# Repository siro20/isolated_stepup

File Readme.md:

# Isolated 12VDC to 300VDC SMPS

This project is about finding a power supply to drive regular 240VAC/120VAC
LED bulbs from a 12V power supply or 12V battery.

This is the first prototype build using the [LTC3723](https://www.analog.com/media/en/technical-documentation/data-sheets/372312f.pdf).

It features:
- Up to 32 Watts
- LC input filter
- Soft-start
- 3 Amps input current limit
- Galvanic isolation
- Adjustable output voltage (for development only)

## Analysis

Measured results of version `0.2`.
- [soft-start](doc/softstart.md)

## Schematics

## Safety advice

    Design, installation and inspection of machinery and devices carrying high voltage
    require accordingly trained and qualified personnel.
    Appropriate safety rules and directives must be complied with.
    Improper handling of high voltage can mean severe injuries or death and may cause
    serious collateral damage! 

## Disclaimer

    THE OPEN SOURCE SOFTWARE/HARDWARE IN THIS PROJECT IS DISTRIBUTED
    IN THE HOPE THAT IT WILL BE USEFUL, BUT WITHOUT ANY WARRANTY, WITHOUT
    EVEN THE IMPLIED WARRANTY OF MERCHANTABILITY OR FITNESS FOR A
    PARTICULAR PURPOSE.

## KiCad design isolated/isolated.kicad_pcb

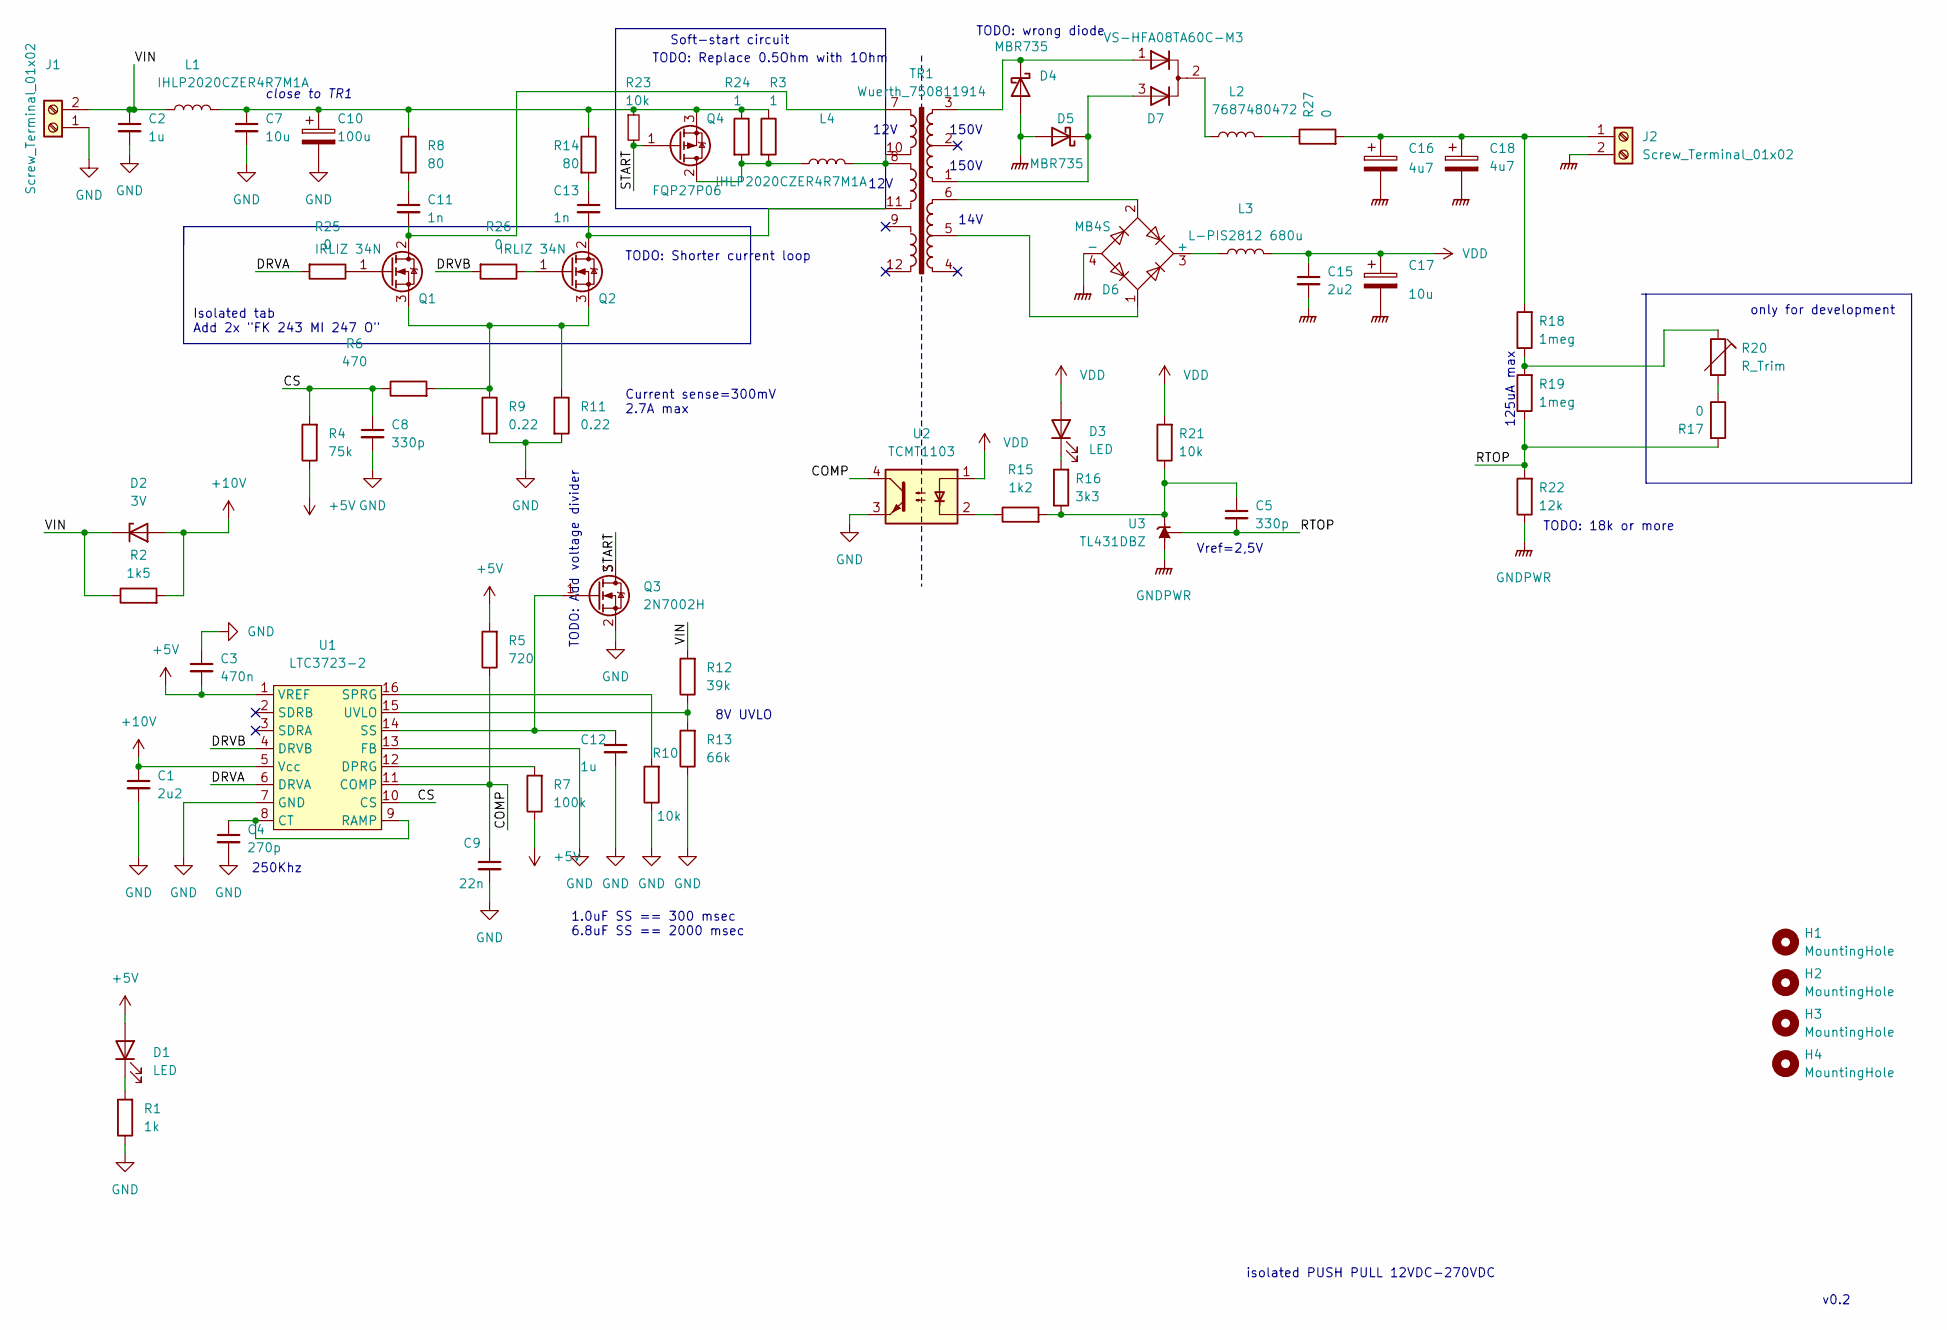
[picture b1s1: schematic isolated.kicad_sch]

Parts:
C1, C15: 2u2; C_1210_3225Metric_Pad1.33x2.70mm_HandSolder
C2, C12: 1u; C_1210_3225Metric_Pad1.33x2.70mm_HandSolder
C3: 470n; C_0805_2012Metric_Pad1.18x1.45mm_HandSolder
C4: 270p; C_0603_1608Metric_Pad1.08x0.95mm_HandSolder
C5, C8: 330p; C_0603_1608Metric_Pad1.08x0.95mm_HandSolder
C7: 10u; C_1210_3225Metric_Pad1.33x2.70mm_HandSolder
C9: 22n; C_0603_1608Metric_Pad1.08x0.95mm_HandSolder
C10: 100u; C_Radial_D10.0mm_H12.5mm_P5.00mm
C11, C13: 1n; C_0805_2012Metric_Pad1.18x1.45mm_HandSolder
C16, C18: 4u7; C_Radial_D12.5mm_H20.0mm_P5.00mm
C17: 10u; C_Radial_D8.0mm_H11.5mm_P3.50mm
D1, D3: LED; LED_D3.0mm_Clear
D2: 3V; D_DO-34_SOD68_P2.54mm_Vertical_KathodeUp
D4, D5: MBR735; TO-220-2_Vertical
D6: MB4S; TO-269AA
D7: VS-HFA08TA60C-M3; TO-220-3_Vertical
H1, H2, H3, H4: MountingHole; MountingHole_2.7mm_M2.5_DIN965_Pad
J1, J2: Screw_Terminal_01x02; PhoenixContact_MCV_1,5_2-G-5.08_1x02_P5.08mm_Vertical
L1, L4: IHLP2020CZER4R7M1A; L_Sunlord_MWSA05xxS
L2: 7687480472; L_Radial_D12.0mm_P5.00mm_Neosid_SD12_style2
L3: L-PIS2812 680u; L_Vishay_IHLP-2020
Q1, Q2: IRLIZ 34N; TO-220-3_Vertical
Q3: 2N7002H; SOT-23
Q4: FQP27P06; TO-220-3_Vertical
R1: 1k; R_0805_2012Metric_Pad1.20x1.40mm_HandSolder
R2: 1k5; R_0805_2012Metric_Pad1.20x1.40mm_HandSolder
R3, R24: 1; R_1206_3216Metric_Pad1.30x1.75mm_HandSolder
R4: 75k; R_0805_2012Metric_Pad1.20x1.40mm_HandSolder
R5: 720; R_0805_2012Metric_Pad1.20x1.40mm_HandSolder
R6: 470; R_0805_2012Metric_Pad1.20x1.40mm_HandSolder
R7: 100k; R_0805_2012Metric_Pad1.20x1.40mm_HandSolder
R8, R14: 80; R_1206_3216Metric_Pad1.30x1.75mm_HandSolder
R9, R11: 0.22; R_2512_6332Metric_Pad1.40x3.35mm_HandSolder
R10, R21, R23: 10k; R_0805_2012Metric_Pad1.20x1.40mm_HandSolder
R12: 39k; R_0805_2012Metric_Pad1.20x1.40mm_HandSolder
R13: 66k; R_0805_2012Metric_Pad1.20x1.40mm_HandSolder
R15: 1k2; R_0805_2012Metric_Pad1.20x1.40mm_HandSolder
R16: 3k3; R_0805_2012Metric_Pad1.20x1.40mm_HandSolder
R17: 0; R_0805_2012Metric
R18: 1meg; R_Axial_DIN0309_L9.0mm_D3.2mm_P5.08mm_Vertical
R19: 1meg; R_Axial_DIN0207_L6.3mm_D2.5mm_P5.08mm_Vertical
R20: R_Trim; Potentiometer_Bourns_3386C_Horizontal
R22: 12k; R_0805_2012Metric_Pad1.20x1.40mm_HandSolder
R25, R26: 0; R_0805_2012Metric_Pad1.20x1.40mm_HandSolder
R27: 0; R_1206_3216Metric_Pad1.30x1.75mm_HandSolder
TR1: Wuerth_750811914; 750811914
U1: LTC3723-2; SSOP-16_3.9x4.9mm_P0.635mm
U2: TCMT1103; SOP-4_4.4x2.6mm_P1.27mm
U3: TL431DBZ; SOT-23

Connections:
+5V: C3.2, D1.2 (A), R4.1, R5.2, R7.1, U1.1 (VREF)
+10V: C1.1, D2.2 (A), R2.2, U1.5 (Vcc)
/COMP: C9.1, R5.1, U1.11 (COMP), U2.4
/CS: C8.1, R4.2, R6.1, U1.10 (CS)
/DRVA: R25.2, U1.6 (DRVA)
/DRVB: R26.2, U1.4 (DRVB)
/RTOP: C5.2, R17.2, R19.1, R22.2, U3.2 (REF)
/START: Q3.3 (D), Q4.1 (G), R23.2
/VIN: C2.1, D2.1 (K), J1.2, L1.1, R2.1, R12.2
GND: C1.2, C2.2, C3.1, C4.2, C7.2, C8.2, C9.2, C10.2, C12.2, J1.1, Q3.2 (S), R1.1, R9.2, R10.1, R11.2, R13.1, U1.7 (GND), U1.13 (FB), U2.3
GNDPWR: C15.2, C16.2, C17.2, C18.2, D4.2 (A), D5.2 (A), D6.4 (-), J2.2, R22.1, U3.3 (A)
unnamed: C4.1, U1.8 (CT), U1.9 (RAMP)
unnamed: C5.1, R15.2, R16.1, R21.1, U3.1 (K)
unnamed: C11.1, R8.2
unnamed: C11.2, Q1.2 (D), TR1.7
unnamed: C12.1, Q3.1 (G), U1.14 (SS)
unnamed: C13.1, R14.2
unnamed: C13.2, Q2.2 (D), TR1.11
unnamed: C16.1, C18.1, J2.1, R18.2, R27.2
unnamed: D1.1 (K), R1.2
unnamed: D3.1 (K), R16.2
unnamed: D4.1 (K), D7.1 (K), TR1.3
unnamed: D5.1 (K), D7.3 (K), TR1.1
unnamed: D7.2 (A), L2.1
unnamed: L2.2, R27.1
unnamed: D6.3 (+), L3.1
unnamed: L4.1, Q4.2 (D), R3.2, R24.2
unnamed: L4.2, TR1.8, TR1.10
unnamed: Q1.1 (G), R25.1
unnamed: Q2.1 (G), R26.1
unnamed: Q1.3 (S), Q2.3 (S), R6.2, R9.1, R11.1
unnamed: C7.1, C10.1, L1.2, Q4.3 (S), R3.1, R8.1, R14.1, R23.1, R24.1
unnamed: R7.2, U1.12 (DPRG)
unnamed: R10.2, U1.16 (SPRG)
unnamed: R12.1, R13.2, U1.15 (UVLO)
unnamed: R15.1, U2.2
unnamed: R17.1, R20.2
unnamed: R18.1, R19.2, R20.1
unnamed: D6.1, TR1.5
unnamed: D6.2, TR1.6
VDD: C15.1, C17.1, D3.2 (A), L3.2, R21.2, U2.1

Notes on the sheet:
12V
TODO: 18k or more
Isolated tab Add 2x "FK 243 MI 247 O"
TODO: Add voltage divider
150V
only for development
250Khz
TODO: Shorter current loop
1.0uF SS == 300 msec 6.8uF SS == 2000 msec
Soft-start circuit
Vref=2,5V
8V UVLO
close to TR1
TODO: Replace 0.5Ohm with 1Ohm
v0.2
125uA max
TODO: wrong diode
Current sense=300mV 2.7A max
isolated PUSH PULL 12VDC-270VDC
14V

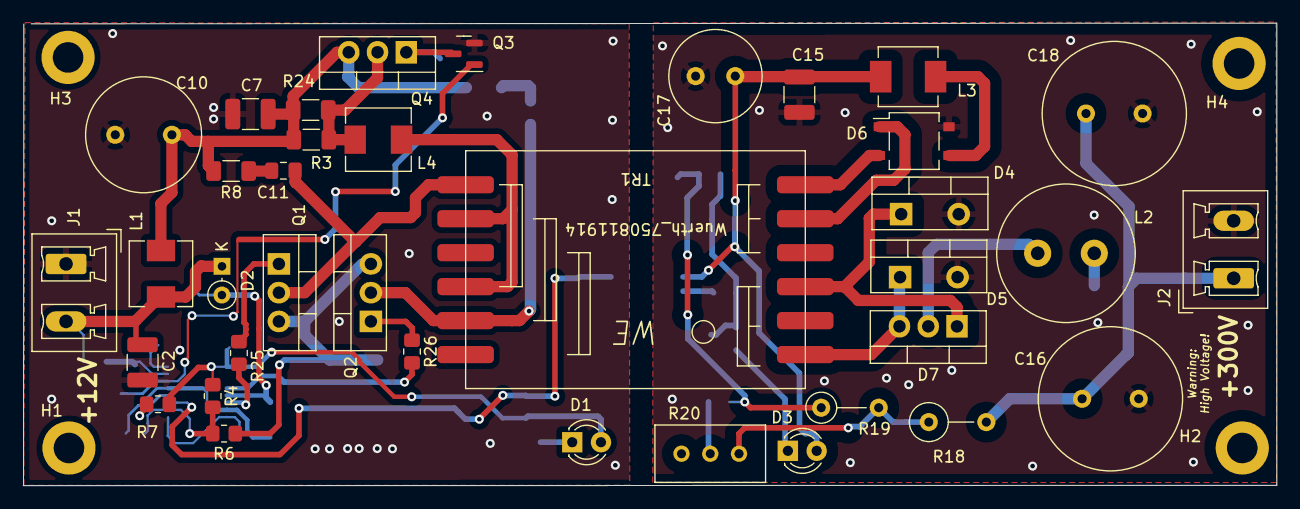
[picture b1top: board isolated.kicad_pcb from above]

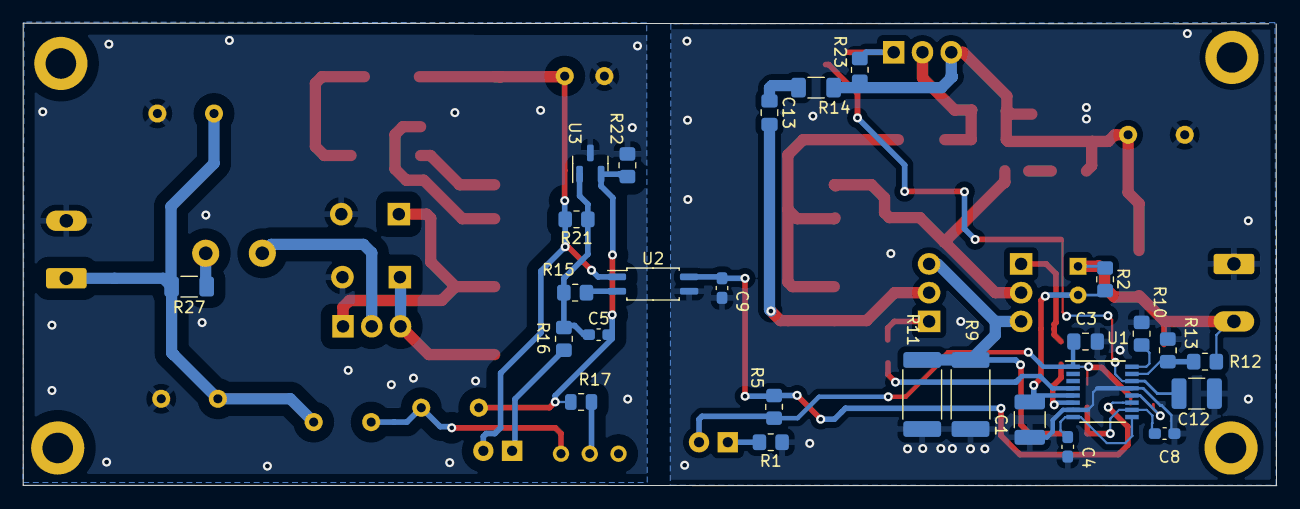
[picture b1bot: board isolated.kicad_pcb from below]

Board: 2 copper layers, 110.7 x 40.8 mm, 68 parts (27 on the bottom side), 41 nets.

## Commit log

2023-04-10 Initial commit
    - add kicad files
    - add Readme
    - add License
    - add gitignore
2023-04-10 Minor fixes
2023-04-22 kicad: Minor cleanups
    - Replace LT1431 with TL431.
2023-05-10 Readme: Document issues found on the PCB
2023-05-28 kicad: Fix issues found in v0.1
    - Change SOIC to SSOP package
    - Fix MB4S pinout
2023-07-31 doc/kicad: Update to revision v0.2
    Fix the problems found in revision v0.1.
    Revision v0.2 works much better and is able to power a
    4W 240VAC LED bulb using 270VDC.
    There are a couple of things to improve though.
